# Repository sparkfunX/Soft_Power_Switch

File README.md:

SparkX Soft Power Switch
===================================================

[*SparkX Soft Power Switch (SPX-17870)*](https://www.sparkfun.com/products/17870)

The Soft Power Switch is a passive, hard on/off switch with software feedback and control. In other words, it's like the on/off switch on a laptop. A simple press will turn the system on. Another press can (with MCU intervention) turn off the system. And if things go really wrong, pressing and holding the button will force a power-down. If you're building something with an enclosed battery and need a good power button, this is the board you need.

The Sense/Control pin can act as an output to a microcontroller indicating the state of the power button (high = not pressed, low = user in pressing power button). This can be used as an input to your firmware to begin to shut down before power is lost. Alternatively, the Sense/Control pin can be driven low by the system forcing power off via software. Additionally, the Fast Off pin can be used to immediately power down a system.

The most common use case is something like this:

* Microcontroller begins running code and checks to see if power button is still being pressed for X milliseconds.
* If not, it's just a tap, go back to sleep.
* If yes, power up and run normal program.

Later...

* User presses power button in normal program
* If power button is pressed for <X milliseconds, it's just a tap, ignore.
* If power button is pressed for >X milliseconds, it's time to power down.

The wake-up and power-down times can be tweaked for your own user experience but we found 500ms for power up and 2s for power down work really well.

If needed, pads are provided for a larger, external button. A measurement jumper is available to measure passive and active current so you can verify the quiescent current of your system.

The Soft Power Switch supports battery charging. If the target device has onboard LiPo charging, current can be passed back through the cut-off circuit and charge the battery.

The Soft Power Switch works up to 12V. There is a 3.3V clamping diode to prevent over-voltage exposure.

The current design is good but has a few problems. The 22uF cap we used requires an override time of 13 seconds. Under normal operation, the system will power down as quickly as you define in the code (1-2s) so users will rarely experience this. But if the system locks up, 13s is a long time to wait. We've also seen a few edge cases (low load or no load) where the override cut-off occurs only after the button is held for >13s and then released. This is caused by shorting between the finger on the button and the near by capacitor. Using an external button allows the unit to power down correctly every time.

We'll continue to refine the design but it's really handy as it is so we decided to release it!

Pros:

* Very low <50nA quiescent current
* Hard override power down in case your microcontroller loses its mind
* Sense/Control pin can be connected to a microcontroller 

Cons:

* Limited to 4A
* No AC loads

Repository Contents
-------------------
* **/Firmware** - Example sketches demonstrating how to read and control the switch
* **/Hardware** - Eagle design files (.brd, .sch)
* **LICENSE.md** - license information

Product Versions
----------------
* [SPX-17870](https://www.sparkfun.com/products/17870) - Original SparkX Release.

License Information
-------------------

This product is _**open source**_!

Please review the LICENSE.md file for license information.

If you have any questions or concerns on licensing, please contact technical support on our [SparkFun forums](https://forum.sparkfun.com/viewforum.php?f=123).

Distributed as-is; no warranty is given.

- Your friends at SparkFun.

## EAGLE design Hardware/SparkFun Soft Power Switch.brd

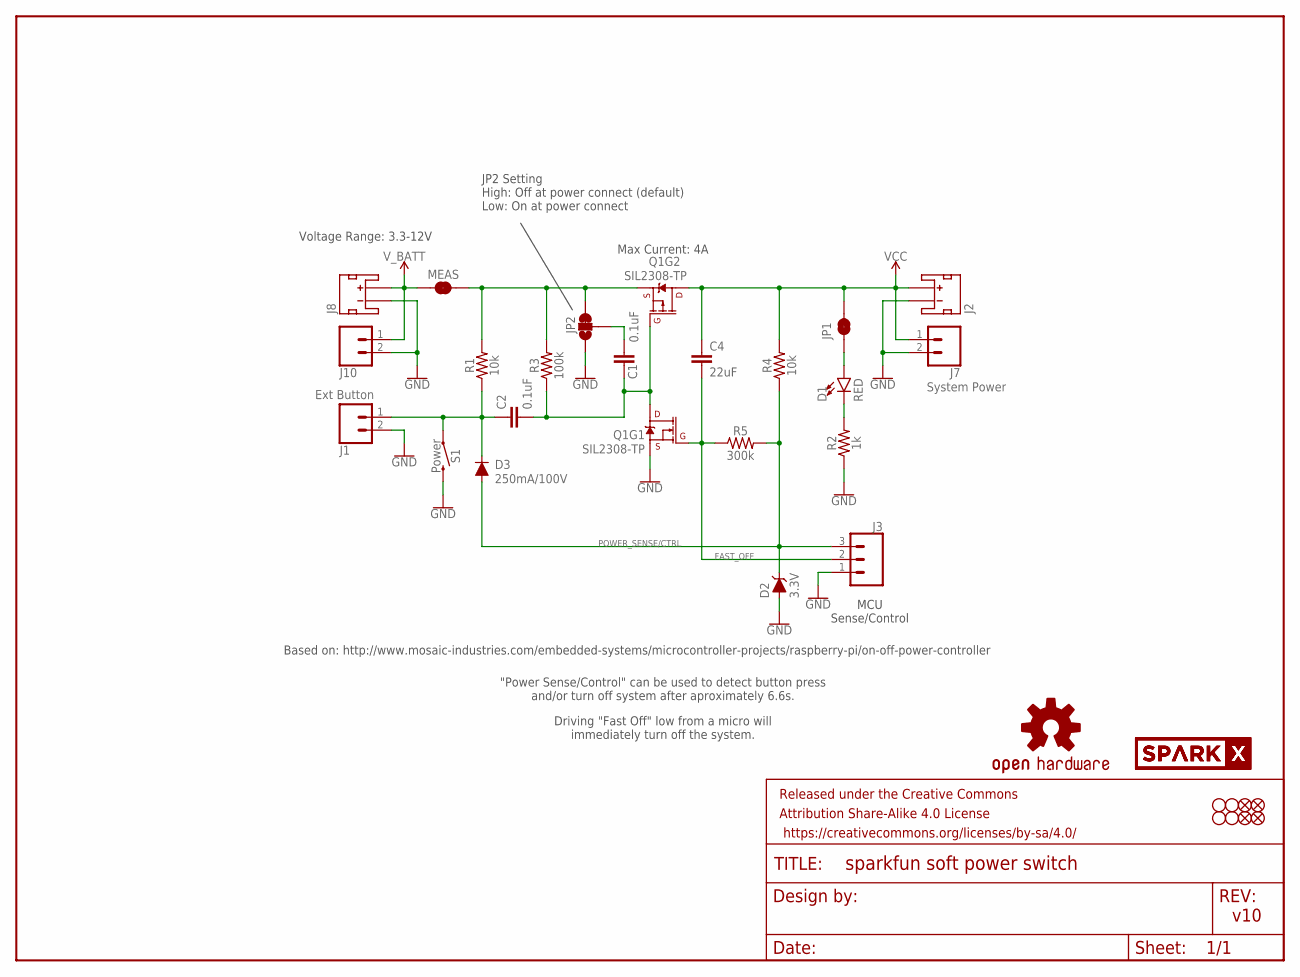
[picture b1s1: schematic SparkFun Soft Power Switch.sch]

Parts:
C1, C2: 0.1uF; 0603
C4: 22uF; 0805
D1: RED; LED-0603
D2: 3.3V; SOD-323
D3: 250mA/100V; SOD-323
FD1, FD2, FD3, FD4: FIDUCIAL1X2; FIDUCIAL-1X2
FRAME1: FRAME-LETTER; CREATIVE_COMMONS
H1, H2, H3, H4: STAND-OFF
J1: Ext Button; 1X02_NO_SILK
J2, J8: JST_2MM_MALE; JST-2-SMD
J3: CONN_031X03_NO_SILK; 1X03_NO_SILK
J7: System Power; 1X02_NO_SILK
J10: CONN_021X02_NO_SILK; 1X02_NO_SILK
JP1: JUMPER-SMT_2_NC_TRACE_SILK; SMT-JUMPER_2_NC_TRACE_SILK
JP2: JUMPER-SMT_3_1-NC_TRACE_SILK; SMT-JUMPER_3_1-NC_TRACE_SILK
LOGO1: OSHW-LOGOS; OSHW-LOGO-S
MEAS: JUMPER-COMBO_2_NC_TRACE; COMBO-JUMPER_2_NC_TRACE
Q1: SIL2308-TP; SOT26
R1, R4: 10k; 0603
R2: 1k; 0603
R3: 100k; 0603
R5: 300k; 0603
S1: Power; TACTILE_SWITCH_SMD_5.2MM
U$1: SPARKX-LOGO3; SPARKX-SMALL
U$15: SPARKX-LOGO2; SPARKX-TINY

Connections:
FAST_OFF: C4.2, J3.2, Q1.G1 (G), R5.1
GND: D2.A, J1.2, J2.1 (-), J3.1, J7.2, J8.1 (-), J10.2, JP2.1, Q1.S1 (S), R2.1, S1.3 (2)
unnamed: C1.2, JP2.2
unnamed: D1.A, JP1.1
unnamed: D1.C, R2.2
unnamed: C1.1, C2.2, Q1.D1 (D), Q1.G2 (G), R3.1
POWER_BTN: C2.1, D3.C, J1.1, R1.1, S1.1
POWER_SENSE/CTRL: D2.C, D3.A, J3.3, R4.1, R5.2
VCC: C4.1, J2.2 (+), J7.1, JP1.2, Q1.D2 (D), R4.2
V_BATT: J8.2 (+), J10.1, MEAS.1, MEAS.3 (1)
V_IN: JP2.3, MEAS.2, MEAS.4 (2), Q1.S2 (S), R1.2, R3.2

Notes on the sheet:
v10
Voltage Range: 3.3-12V
Based on: http://www.mosaic-industries.com/embedded-systems/microcontroller-projects/raspberry-pi/on-off-power-controller
Max Current: 4A
JP2 Setting High: Off at power connect (default) Low: On at power connect
MCU Sense/Control
"Power Sense/Control" can be used to detect button press and/or turn off system after aproximately 6.6s.
Driving "Fast Off" low from a micro will immediately turn off the system.

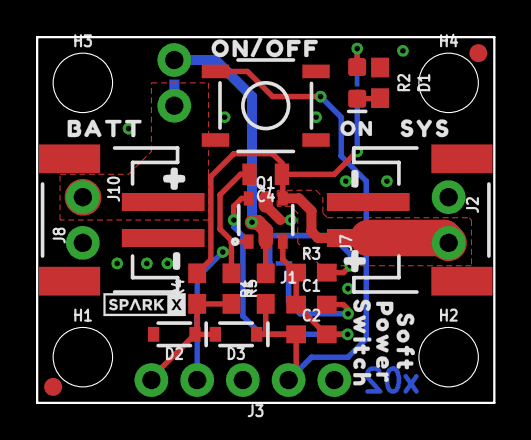
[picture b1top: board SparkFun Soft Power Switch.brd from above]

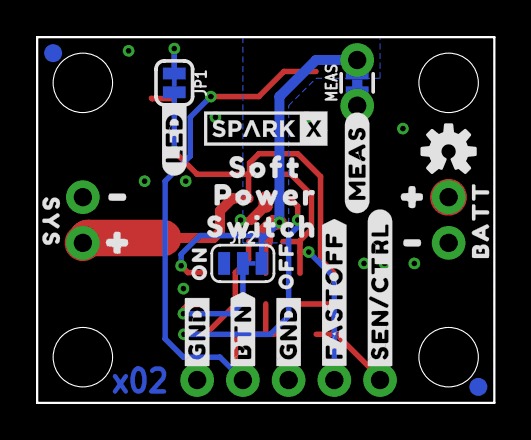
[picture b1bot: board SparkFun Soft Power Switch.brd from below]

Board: 2 copper layers, 25.4 x 20.3 mm, 63 parts (25 on the bottom side), 11 nets.

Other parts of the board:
U$2: #BTN#2
U$3, U$4: #GND#0
U$5: #SEN#CTRL#1
U$6: ON#OFF0
U$7, U$29: BATT0
U$8, U$31: SYS1
U$9, U$10, U$14, U$22: #0
U$11, U$12, U$20, U$23: #1
U$13: #MEAS#0
U$16: OFF1
U$17: SWITCH2
U$18, U$25: ON0
U$19: #LED#0
U$21: SOFT_0
U$24: POWER_1
U$26: #FASTOFF#0
U$27: SOFT0
U$28: POWER1
U$30: SWITCH_2

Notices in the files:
parts and their libraries:
SparkFun-Aesthetics: Licensing: Creative Commons ShareAlike 4.0 International - https://creativecommons.org/licenses/by-sa/4.0
SparkFun-Aesthetics: Released under the Creative Commons Attribution Share-Alike 4.0 License
SparkFun-Aesthetics: https://creativecommons.org/licenses/by-sa/4.0
